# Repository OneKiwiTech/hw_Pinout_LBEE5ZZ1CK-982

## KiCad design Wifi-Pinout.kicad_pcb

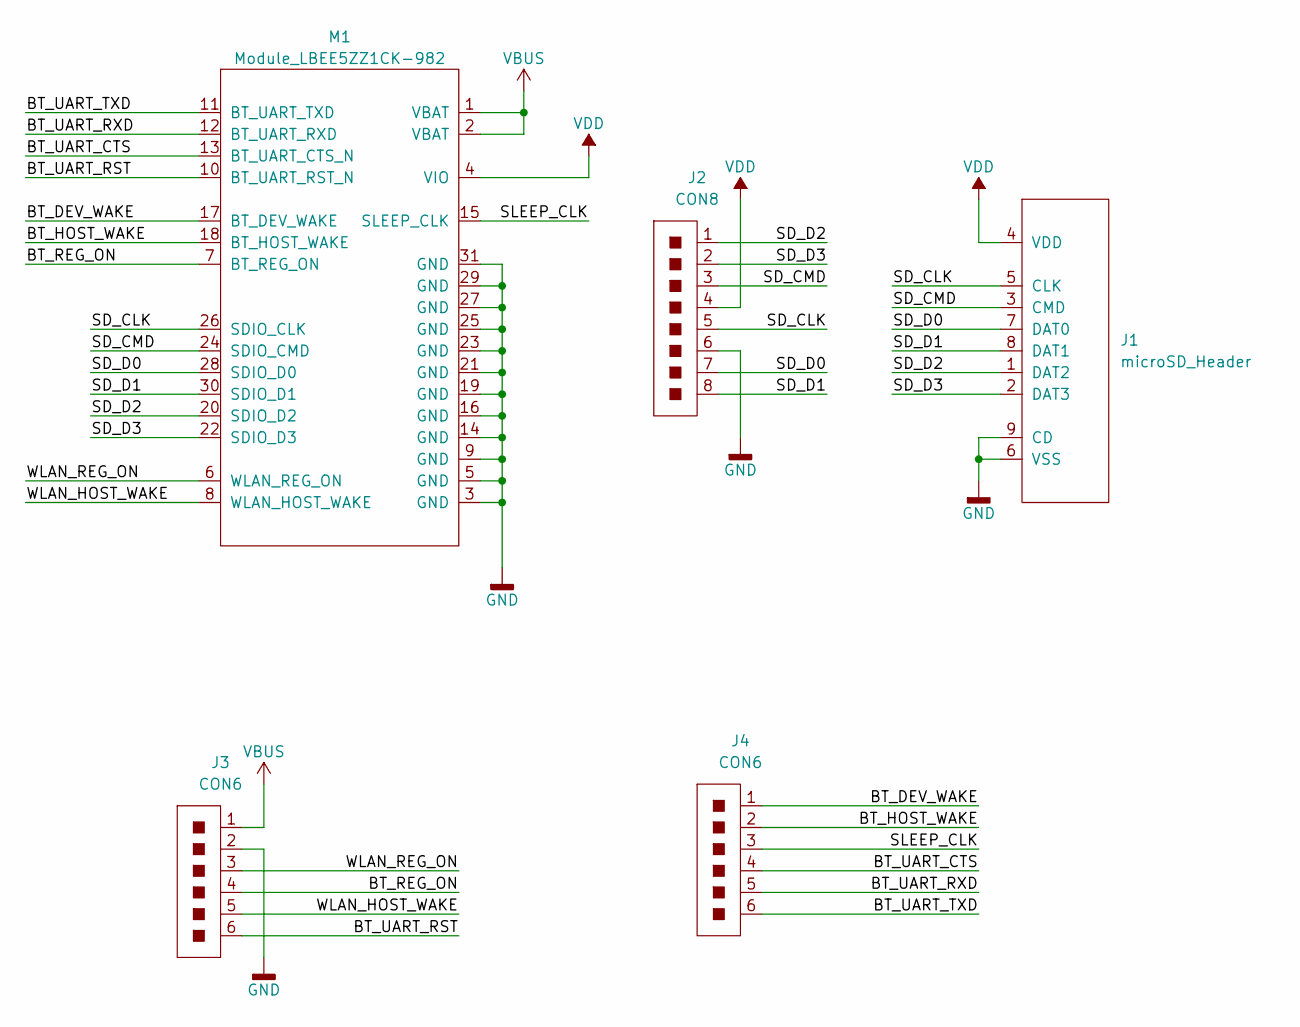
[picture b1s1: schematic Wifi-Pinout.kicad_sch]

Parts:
J1: microSD_Header; microSD_Header_GCT
J2: CON8; HDR_P2.54_1x8
J3, J4: CON6; HDR_P2.54_1x6
M1: Module_LBEE5ZZ1CK-982; LBEE5ZZ1CK-982

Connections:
/BT_DEV_WAKE: J4.1, M1.17 (BT_DEV_WAKE)
/BT_HOST_WAKE: J4.2, M1.18 (BT_HOST_WAKE)
/BT_REG_ON: J3.4, M1.7 (BT_REG_ON)
/BT_UART_CTS: J4.4, M1.13 (BT_UART_CTS_N)
/BT_UART_RST: J3.6, M1.10 (BT_UART_RST_N)
/BT_UART_RXD: J4.5, M1.12 (BT_UART_RXD)
/BT_UART_TXD: J4.6, M1.11 (BT_UART_TXD)
/SD_CLK: J1.5 (CLK), J2.5, M1.26 (SDIO_CLK)
/SD_CMD: J1.3 (CMD), J2.3, M1.24 (SDIO_CMD)
/SD_D0: J1.7 (DAT0), J2.7, M1.28 (SDIO_D0)
/SD_D1: J1.8 (DAT1), J2.8, M1.30 (SDIO_D1)
/SD_D2: J1.1 (DAT2), J2.1, M1.20 (SDIO_D2)
/SD_D3: J1.2 (DAT3), J2.2, M1.22 (SDIO_D3)
/SLEEP_CLK: J4.3, M1.15 (SLEEP_CLK)
/WLAN_HOST_WAKE: J3.5, M1.8 (WLAN_HOST_WAKE)
/WLAN_REG_ON: J3.3, M1.6 (WLAN_REG_ON)
GND: J1.6 (VSS), J1.9 (CD), J2.6, J3.2, M1.3 (GND), M1.5 (GND), M1.9 (GND), M1.14 (GND), M1.16 (GND), M1.19 (GND), M1.21 (GND), M1.23 (GND), M1.25 (GND), M1.27 (GND), M1.29 (GND), M1.31 (GND)
VBUS: J3.1, M1.1 (VBAT), M1.2 (VBAT)
VDD: J1.4 (VDD), J2.4, M1.4 (VIO)

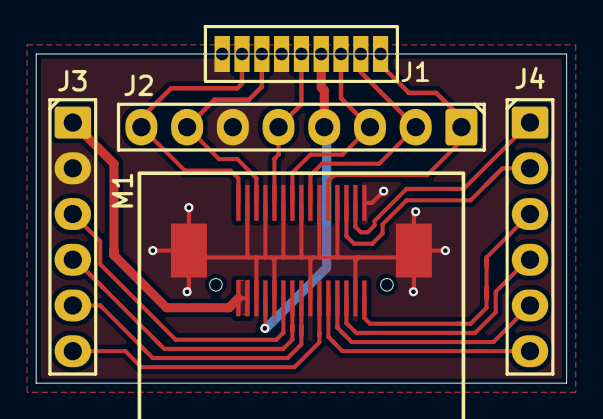
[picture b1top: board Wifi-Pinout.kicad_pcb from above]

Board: 2 copper layers, 29.5 x 18.3 mm, 5 parts (0 on the bottom side), 19 nets.
